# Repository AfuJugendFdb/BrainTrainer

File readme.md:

BrainTrainer
----------------

Bausatz Ferienprogramm 2016
Simon Says mit 4 LEDs, die in zufälliger Reihenfolge aufleuchten und deren Abfolge mit den entsprechenden 4 Tastern reproduziert werden müssen.
Jetzt mit fancy Correct-, Fail- und LevelUp-Sounds

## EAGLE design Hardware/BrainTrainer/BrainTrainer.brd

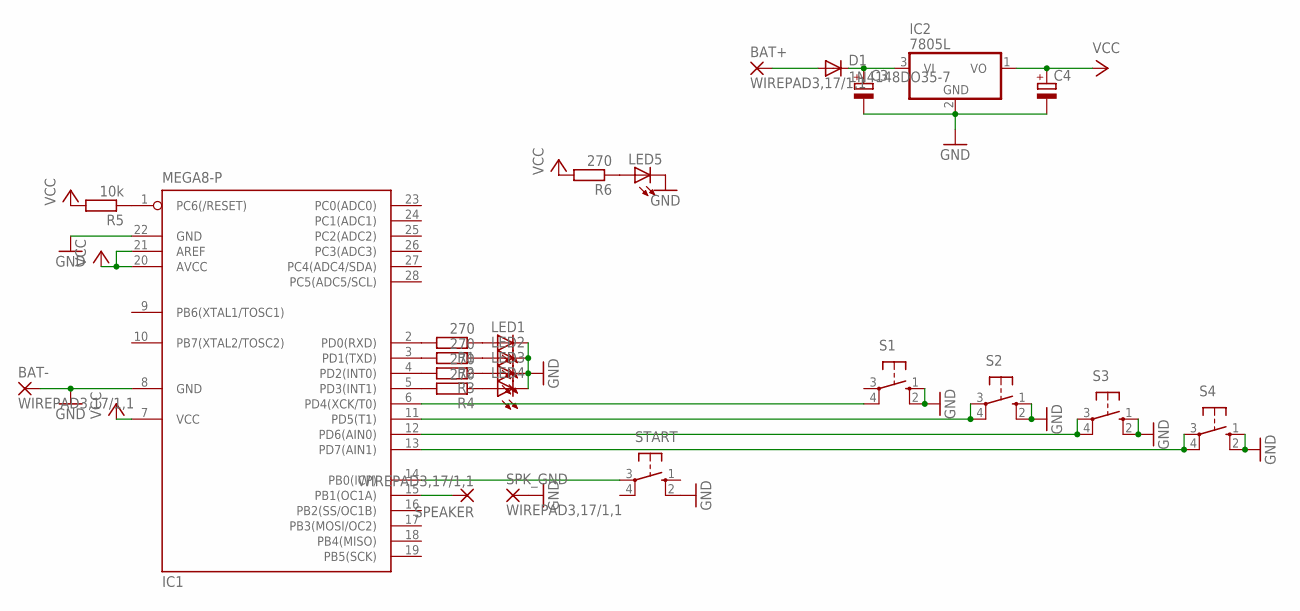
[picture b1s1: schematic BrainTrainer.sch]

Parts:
BAT+: WIREPAD3,17/1,1; 3,17/1,1
BAT-: WIREPAD3,17/1,1; 3,17/1,1
C3, C4: CPOL-EUE2,5-6E; E2,5-6E
D1: 1N4148DO35-7; DO35-7
IC1: MEGA8-P; DIL28-3
IC2: 7805L; TO92
LED1, LED2, LED3, LED4, LED5: LED5MM
R1, R2, R3, R4, R6: 270; 0207/7
R5: 10k; 0207/7
S1, S2, S3, S4: 10-XX; B3F-10XX
SPEAKER: WIREPAD3,17/1,1; 3,17/1,1
SPK_GND: WIREPAD3,17/1,1; 3,17/1,1
START: 10-XX; B3F-10XX

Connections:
GND: BAT-.1, C3.-, C4.-, IC1.8 (GND), IC1.22 (GND), IC2.2 (GND), LED1.K (C), LED2.K (C), LED3.K (C), LED4.K (C), LED5.K (C), S1.1 (S), S1.2 (S1), S2.1 (S), S2.2 (S1), S3.1 (S), S3.2 (S1), S4.1 (S), S4.2 (S1), SPK_GND.1, START.2 (S1)
unnamed: IC1.15 (PB1(OC1A)), SPEAKER.1
unnamed: IC1.2 (PD0(RXD)), R1.2
unnamed: LED1.A, R1.1
unnamed: IC1.3 (PD1(TXD)), R2.2
unnamed: LED2.A, R2.1
unnamed: IC1.4 (PD2(INT0)), R3.2
unnamed: LED3.A, R3.1
unnamed: IC1.5 (PD3(INT1)), R4.2
unnamed: IC1.6 (PD4(XCK/T0)), S1.4 (P1)
unnamed: IC1.11 (PD5(T1)), S2.3, S2.4 (P1)
unnamed: IC1.12 (PD6(AIN0)), S3.3, S3.4 (P1)
unnamed: IC1.13 (PD7(AIN1)), S4.3, S4.4 (P1)
unnamed: BAT+.1, D1.A
unnamed: IC1.14 (PB0(ICP)), START.3
unnamed: LED4.A, R4.1
unnamed: C3.+, D1.C, IC2.3 (VI)
unnamed: IC1.1 (PC6(/RESET)), R5.1
unnamed: LED5.A, R6.1
VCC: C4.+, IC1.7 (VCC), IC1.20 (AVCC), IC1.21 (AREF), IC2.1 (VO), R5.2, R6.2

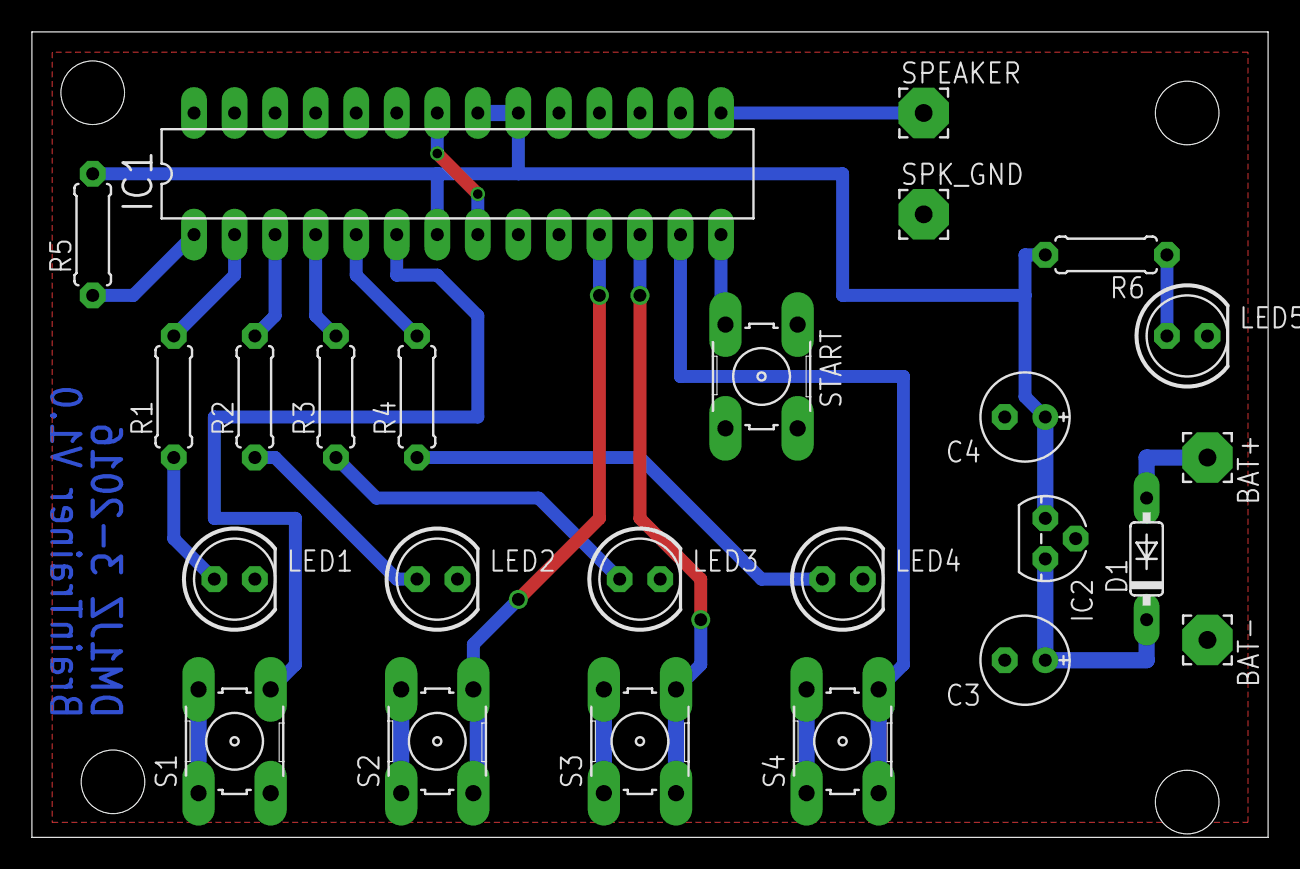
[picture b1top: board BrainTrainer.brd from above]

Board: 2 copper layers, 77.5 x 50.5 mm, 25 parts (0 on the bottom side), 20 nets.

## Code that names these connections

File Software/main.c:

/*************************************
* BrainTrainer: Gedächtnisspiel: Mehrere LEDs leuchten nach zufälligem Muster der Reihe nach auf, der Spieler muss dieses Muster mit den entsprechenden Tastern reproduzieren
* Version 1.1
* 10.09.16 DM1JZ
*
* LEDs an PD0-PD3, Taster an PD4-PD7
*
* ACHTUNG: alle Zugriffe auf PORTD müssen verodert werden, damit die Konfiguration der Pullup-Widerstände nicht verändert wird!
**************************************/

#include <avr/io.h>
#include <util/delay.h>
#include <stdlib.h>
#include "synth.h"

uint8_t generateNumber(void);
uint8_t readKeys(void);
void playError(void);
void playCorrect(void);
void playStartup(void);
void initRandGen(void);
void playLaunchGame(void);
void playLevelUp5(void);

uint8_t pattern[100];	//Hier kommt die LED-Abfolge rein
uint8_t patternPos = 0;	//Zähler, bis zu welcher Position die aktuelle Pattern-Folge geht (wie viele LEDs leuchten auf)
uint8_t input[100];

int main(void)
{
	DDRD = 0x0F; 	//Taster Eingang, LEDs Ausgang
	PORTD = 0xF0;	//Pull-ups an Tastern aktivieren, LEDs aus
	DDRB = (0 << PB0) | (1 << PB1); //PBO: Start-Taster, PB1: Summer
	PORTB |= (1 << PB0); //Pullup an Start-Taster an
	
	synth_init();
	
	_delay_ms(200);
	playStartup();
	_delay_ms(500);
	
	initRandGen(); //Blockierend, wartet, bis Start-Button gedrückt ist
	
	playLaunchGame();
	
	
	while(1)
	{
		//Neue Zufallszahl generieren und dem Pattern hinzufügen
		pattern[patternPos] = generateNumber(); //Achtung: 0-basierend
		
		/*
		//Oder: Komplett neue Pattern-Kette erfinden:
		for(uint8_t i = 0; i <= patternPos; i++)
		{
			pattern[patternPos] = generateNumber();
		}
		*/	
		
		//LED-Muster abspielen
		for(uint8_t i = 0; i <= patternPos; i++)
		{
			PORTD |= (1 << pattern[i]);	//verodern, um Pullup-Widerstände nicht zu ändern! Bit-Stelle stimmt mit 0-basierend überein!
			_delay_ms(500);
			PORTD &= ~(1 << pattern[i]);	//entsprechende LED wieder mit AND abschalten
			_delay_ms(250);
		}
		
		//Taster einlesen
		for(uint8_t i = 0; i <= patternPos; i++)
		{
			input[i] = readKeys();
		}
		
		_delay_ms(500);
		
		//Input mit Pattern vergleichen
		uint8_t correct = 1; //true
		
		for(uint8_t i = 0; i <= patternPos; i++)
		{
			if(input[i] != pattern[i])
			{
				correct = 0; //false
			}
		}
		if(correct == 1)
		{
			patternPos++;
			
			playLevelUp5();
			_delay_ms(500);
			
			playCorrect();
			
		}
		else
		{
			playError();
		}
		
		//Verschnaufpause
		_delay_ms(2000);
	}
	
	return 0;
}

uint8_t generateNumber(void) //Achtung: 0-basierend
{
	uint8_t number = 0;
	
	number = rand()%4;	
		
	return number;
}

uint8_t readKeys(void)
{
	static uint8_t input_new = 0xFF;
	static uint8_t input_old = 0xFF;
	
	while(1)
	{
		input_new = PIND & 0xF0;
		
		if(input_new != input_old)
		{
			input_old = input_new;
			
			if((input_new & 0b00010000) == 0)
			{
				_delay_ms(10);
				input_new = PIND & 0xF0;
				if((input_new & 0b00010000) == 0)
				{
					return 0;
				}
			}
			
			if((input_new & 0b00100000) == 0)
			{
				_delay_ms(10);
				input_new = PIND & 0xF0;
				if((input_new & 0b00100000) == 0)
				{
					return 1;
				}
			}
			
			if((input_new & 0b01000000) == 0)
			{
				_delay_ms(10);
				input_new = PIND & 0xF0;
				if((input_new & 0b01000000) == 0)
				{
					return 2;
				}
			}
			
			if((input_new & 0b10000000) == 0)
			{
				_delay_ms(10);
				input_new = PIND & 0xF0;
				if((input_new & 0b10000000) == 0)
				{
					return 3;
				}
			}
		}
	}
}

void playError(void)
{	
	for(uint8_t i = 0; i < 100; i = i+5)
	{
		playSound(200 + i);
		_delay_ms(50);
	}
	toneOff();
}

void playCorrect(void)
{
	playTone(5, 0);
	_delay_ms(100);
	playTone(5, 7);
	_delay_ms(100);
	toneOff();
}

void playStartup(void)
{
	_delay_ms(500);
	
	playTone(4, 0);
	_delay_ms(100);
	playTone(4, 1);
	_delay_ms(100);
	playTone(4, 2);
	_delay_ms(100);
	playTone(4, 3);
	_delay_ms(100);
	playTone(4, 4);
	_delay_ms(100);
	
	toneOff();
	_delay_ms(100);
	
	playTone(3, 6);
	_delay_ms(100);
	toneOff();
	_delay_ms(100);
	playTone(4, 0);
	_delay_ms(200);
	
	toneOff();
}

void initRandGen(void)
{
	uint8_t time = 0;
	
	//solange Button nicht gedrückt ist, erhöhe Zeit nach kurzer Delayzeit, bis Button gedrückt
	while((PINB & 0x01) != 0)
	{
		time++;
		_delay_ms(1);
	}
	
	srand(time);
}

void playLaunchGame(void)
{
	playTone(4, 0);
	_delay_ms(100);
	playTone(4, 2);
	_delay_ms(300);
	playTone(4, 0);
	_delay_ms(100);
	playTone(4, 4);
	_delay_ms(300);
	playTone(4, 2);
	_delay_ms(100);
	playTone(4, 7);
	_delay_ms(500);
	toneOff();
}

void playLevelUp5(void)
{
	if((patternPos % 5) == 0)
	{
		for(uint8_t i  = 0; i < 8; i++)
		{
			playTone(4, i);
			_delay_ms(50);
		}
		playTone(5, 0);
		_delay_ms(250);
		toneOff();
	}
}

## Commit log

2017-08-04 Small cleanup of out-commented software
